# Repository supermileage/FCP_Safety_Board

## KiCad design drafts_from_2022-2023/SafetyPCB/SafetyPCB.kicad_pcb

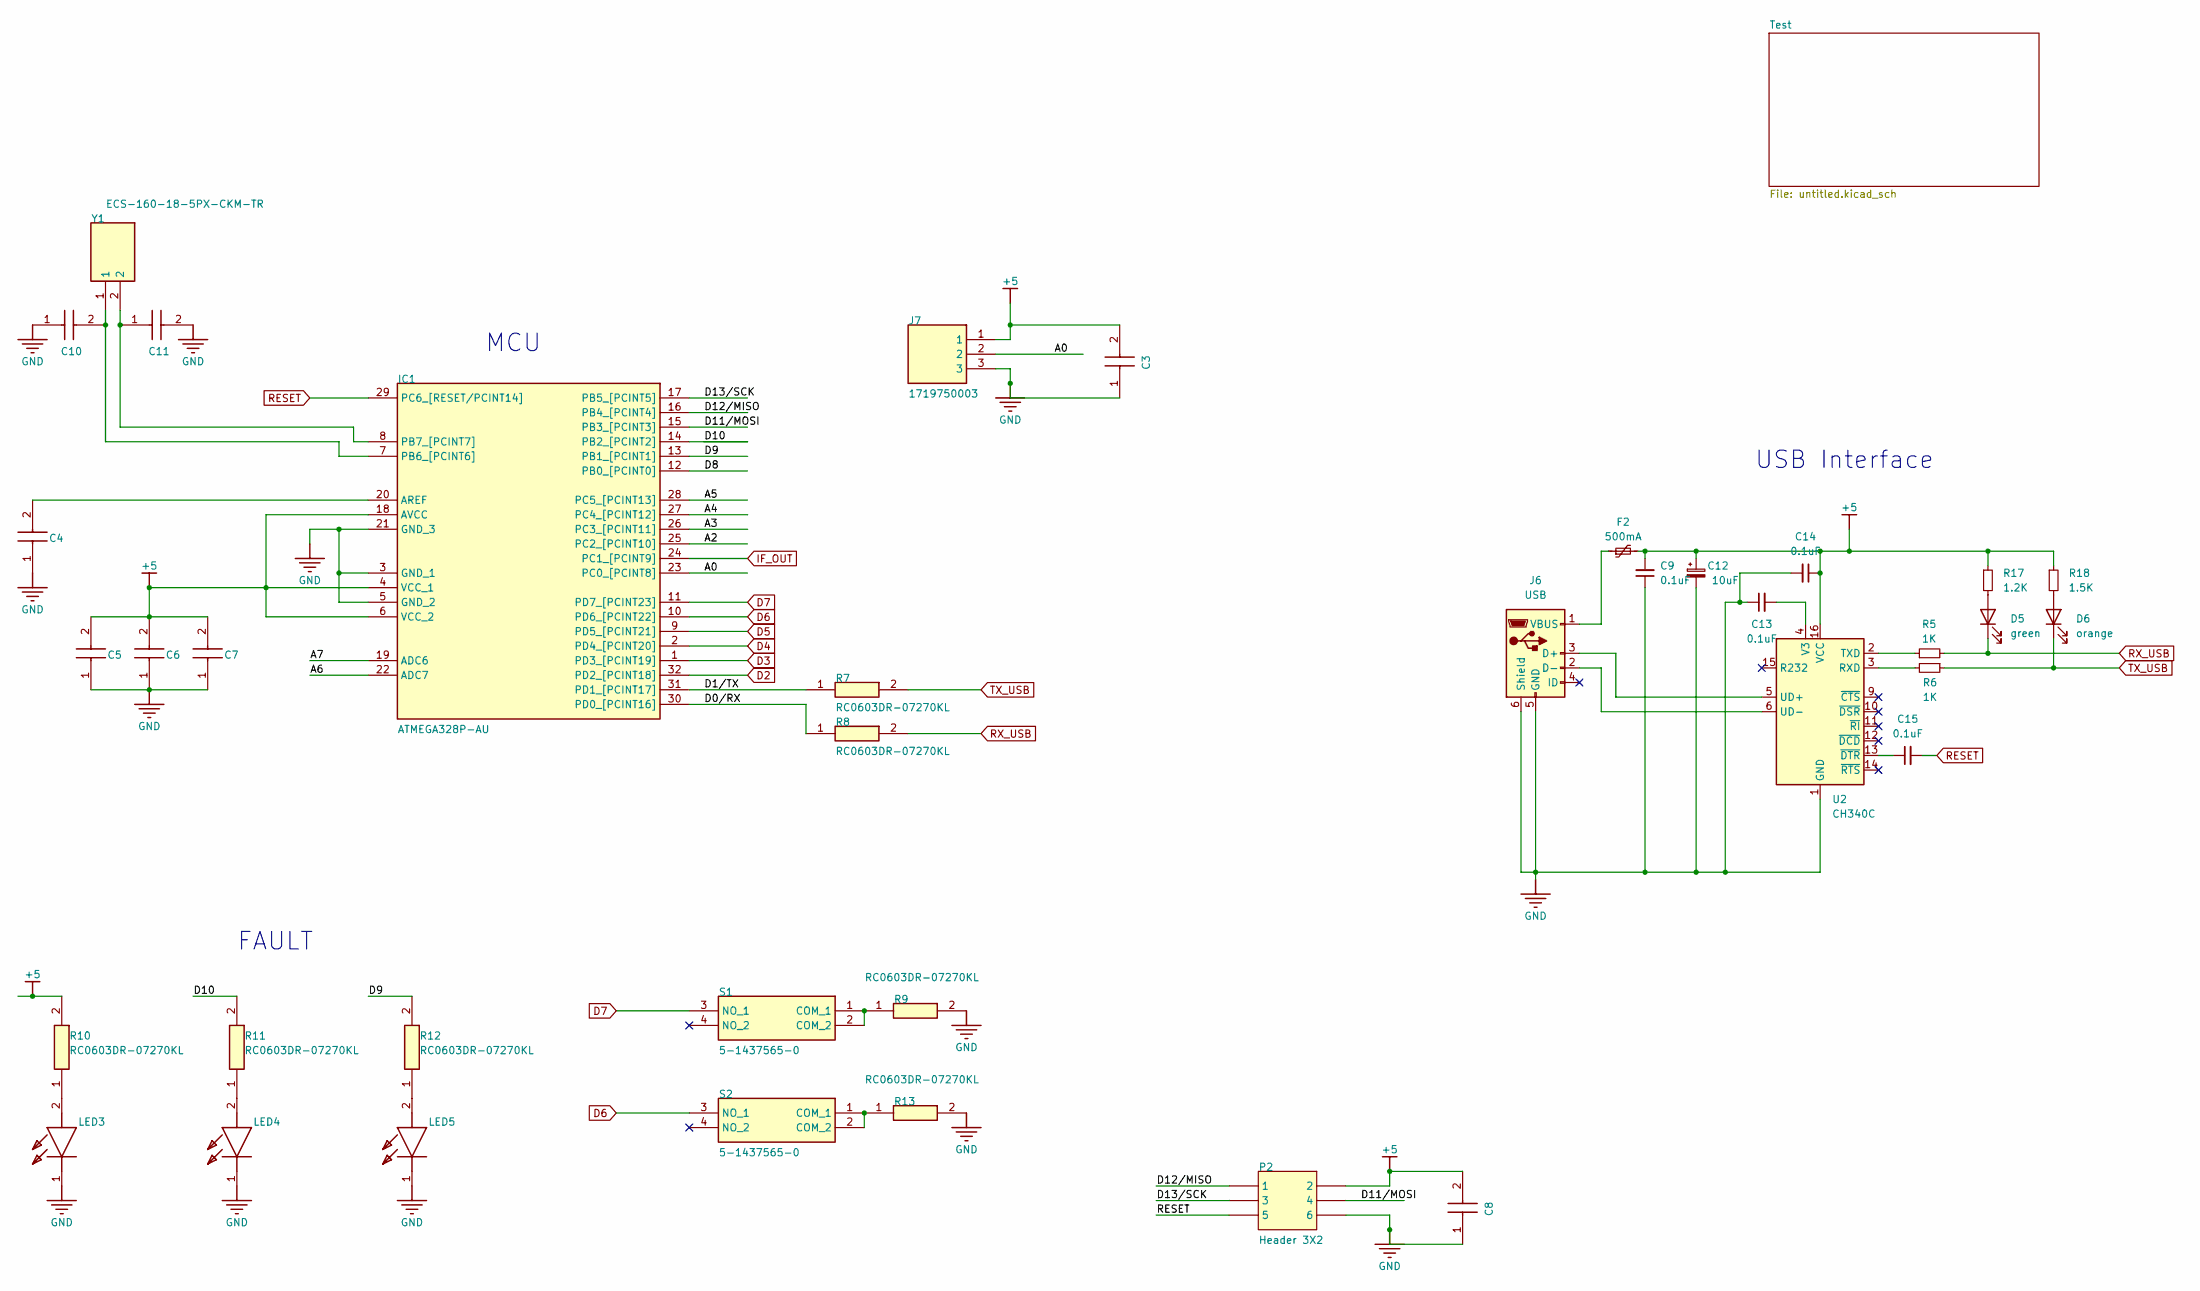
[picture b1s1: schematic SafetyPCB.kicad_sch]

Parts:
C3, C8, C11: 0.1uF; C_0603_1608Metric; MOUSER PART NUMBER 80-C0603C104K3R; digikey part number 399-C0603C104K3RAC7867TR-ND
C4, C5, C6, C7, C10: 0.1uF; C_0603_1608Metric; MOUSER PART NUMBER 80-C0603C104K3R; digikey part number C0603C104K3RACTU
C9, C13, C14, C15: 0.1uF; C_0603_1608Metric
C12: 10uF; C_1206_3216Metric
D5: green; LED_0805_2012Metric
D6: orange; LED_0805_2012Metric
F2: 500mA; Fuse_1206_3216Metric
IC1: ATMEGA328P-AU; QFP80P900X900X120-32N; MANUFACTURER_PART_NUMBER ATMEGA328P-AU; MOUSER PART NUMBER 556-ATMEGA328P-AU
J6: USB; USB_Micro-B_Molex_47346-0001
J7: 1719750003; MOLEX_1719750003; digikey part number 1719750003
LED3, LED4, LED5: LTST-C191TBKT-5A; LED_0201_0603Metric; MOUSER PART NUMBER 859-LTST-C191TBKT-5A; digikey part number LTST-C191TBKT-5A
P2: Header 3X2; PinHeader_2x03_P2.54mm_Vertical
R5, R6: 1K; R_0805_2012Metric
R7, R8, R9, R13: RC0603DR-07270KL; R_0603_1608Metric; digikey part number RC0603DR-07270KL
R10: RC0603DR-07270KL; R_0603_1608Metric; MOUSER PART NUMBER RC0603DR-07270KL-ND - Tape & Reel (TR); digikey part number RC0603DR-07270KL-ND
R11: RC0603DR-07270KL; R_0603_1608Metric; digikey part number RC0603DR-07270KL-ND
R12: RC0603DR-07270KL; R_0603_1608Metric; MANUFACTURER_PART_NUMBER RC0603DR-07270KL; digikey part number RC0603DR-07270KL-ND
R17: 1.2K; R_0805_2012Metric
R18: 1.5K; R_0805_2012Metric
S1, S2: 5-1437565-0; SW_5-1437565-0; MANUFACTURER_PART_NUMBER 5-1437565-0; MOUSER PART NUMBER 506-5-1437565-0
U2: CH340C; SOIC-16_3.9x9.9mm_P1.27mm
Y1: ECS-160-18-5PX-CKM-TR; XTAL_ECS-160-18-5PX-CKM-TR; MANUFACTURER_PART_NUMBER ECS-160-18-5PX-CKM-TR; digikey part number 50-ECS-160-18-5PX-CKM-TR-ND

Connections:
+5: C3.2, C5.2, C6.2, C7.2, C8.2, C9.2, C12.1, C14.1, F2.2, IC1.4 (VCC_1), IC1.6 (VCC_2), IC1.18 (AVCC), J7.1, P2.2, R10.2, R17.1, R18.1, U2.16 (VCC); also elsewhere on the board
/A0: IC1.23 (PC0_[PCINT8]), J7.2
/A2: IC1.25 (PC2_[PCINT10])
/A3: IC1.26 (PC3_[PCINT11])
/A4: IC1.27 (PC4_[PCINT12])
/A5: IC1.28 (PC5_[PCINT13])
/A6: IC1.22 (ADC7)
/A7: IC1.19 (ADC6)
/D0/RX: IC1.30 (PD0_[PCINT16]), R8.1
/D1/TX: IC1.31 (PD1_[PCINT17]), R7.1
/D8: IC1.12 (PB0_[PCINT0])
/D9: IC1.13 (PB1_[PCINT1]), R12.2
/D10: IC1.14 (PB2_[PCINT2]), R11.2
/D11/MOSI: IC1.15 (PB3_[PCINT3]), P2.4
/D12/MISO: IC1.16 (PB4_[PCINT4]), P2.1
/D13/SCK: IC1.17 (PB5_[PCINT5]), P2.3
D2: IC1.32 (PD2_[PCINT18]); also elsewhere on the board
D3: IC1.1 (PD3_[PCINT19]); also elsewhere on the board
D4: IC1.2 (PD4_[PCINT20]); also elsewhere on the board
D5: IC1.9 (PD5_[PCINT21]); also elsewhere on the board
D6: IC1.10 (PD6_[PCINT22]), S2.3 (NO_1)
D7: IC1.11 (PD7_[PCINT23]), S1.3 (NO_1)
GND: C3.1, C4.1, C5.1, C6.1, C7.1, C8.1, C9.1, C10.1, C11.2, C12.2, C13.1, C14.2, IC1.3 (GND_1), IC1.5 (GND_2), IC1.21 (GND_3), J6.5 (GND), J6.6 (Shield), J7.3, LED3.1 (K), LED4.1 (K), LED5.1 (K), P2.6, R9.2, R13.2, U2.1 (GND); also elsewhere on the board
IF_OUT: IC1.24 (PC1_[PCINT9]); also elsewhere on the board
unnamed: C4.2, IC1.20 (AREF)
unnamed: C10.2, IC1.7 (PB6_[PCINT6]), Y1.1
unnamed: C11.1, IC1.8 (PB7_[PCINT7]), Y1.2
unnamed: C13.2, U2.4 (V3)
unnamed: C15.1, U2.13 (~DTR)
unnamed: D5.2 (A), R17.2
unnamed: D6.2 (A), R18.2
unnamed: F2.1, J6.1 (VBUS)
unnamed: J6.2 (D-), U2.6 (UD-)
unnamed: J6.3 (D+), U2.5 (UD+)
unnamed: LED3.2 (A), R10.1
unnamed 45: LED4.2 (A), R11.1; also elsewhere on the board
unnamed 46: LED5.2 (A), R12.1; also elsewhere on the board
unnamed: R5.1, U2.2 (TXD)
unnamed: R6.2, U2.3 (RXD)
unnamed: R9.1, S1.1 (COM_1), S1.2 (COM_2)
unnamed: R13.1, S2.1 (COM_1), S2.2 (COM_2)
RESET: C15.2, IC1.29 (PC6_[RESET/PCINT14]), P2.5
RX_USB: D5.1 (K), R5.2, R8.2
TX_USB: D6.1 (K), R6.1, R7.2

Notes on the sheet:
USB Interface
FAULT
MCU

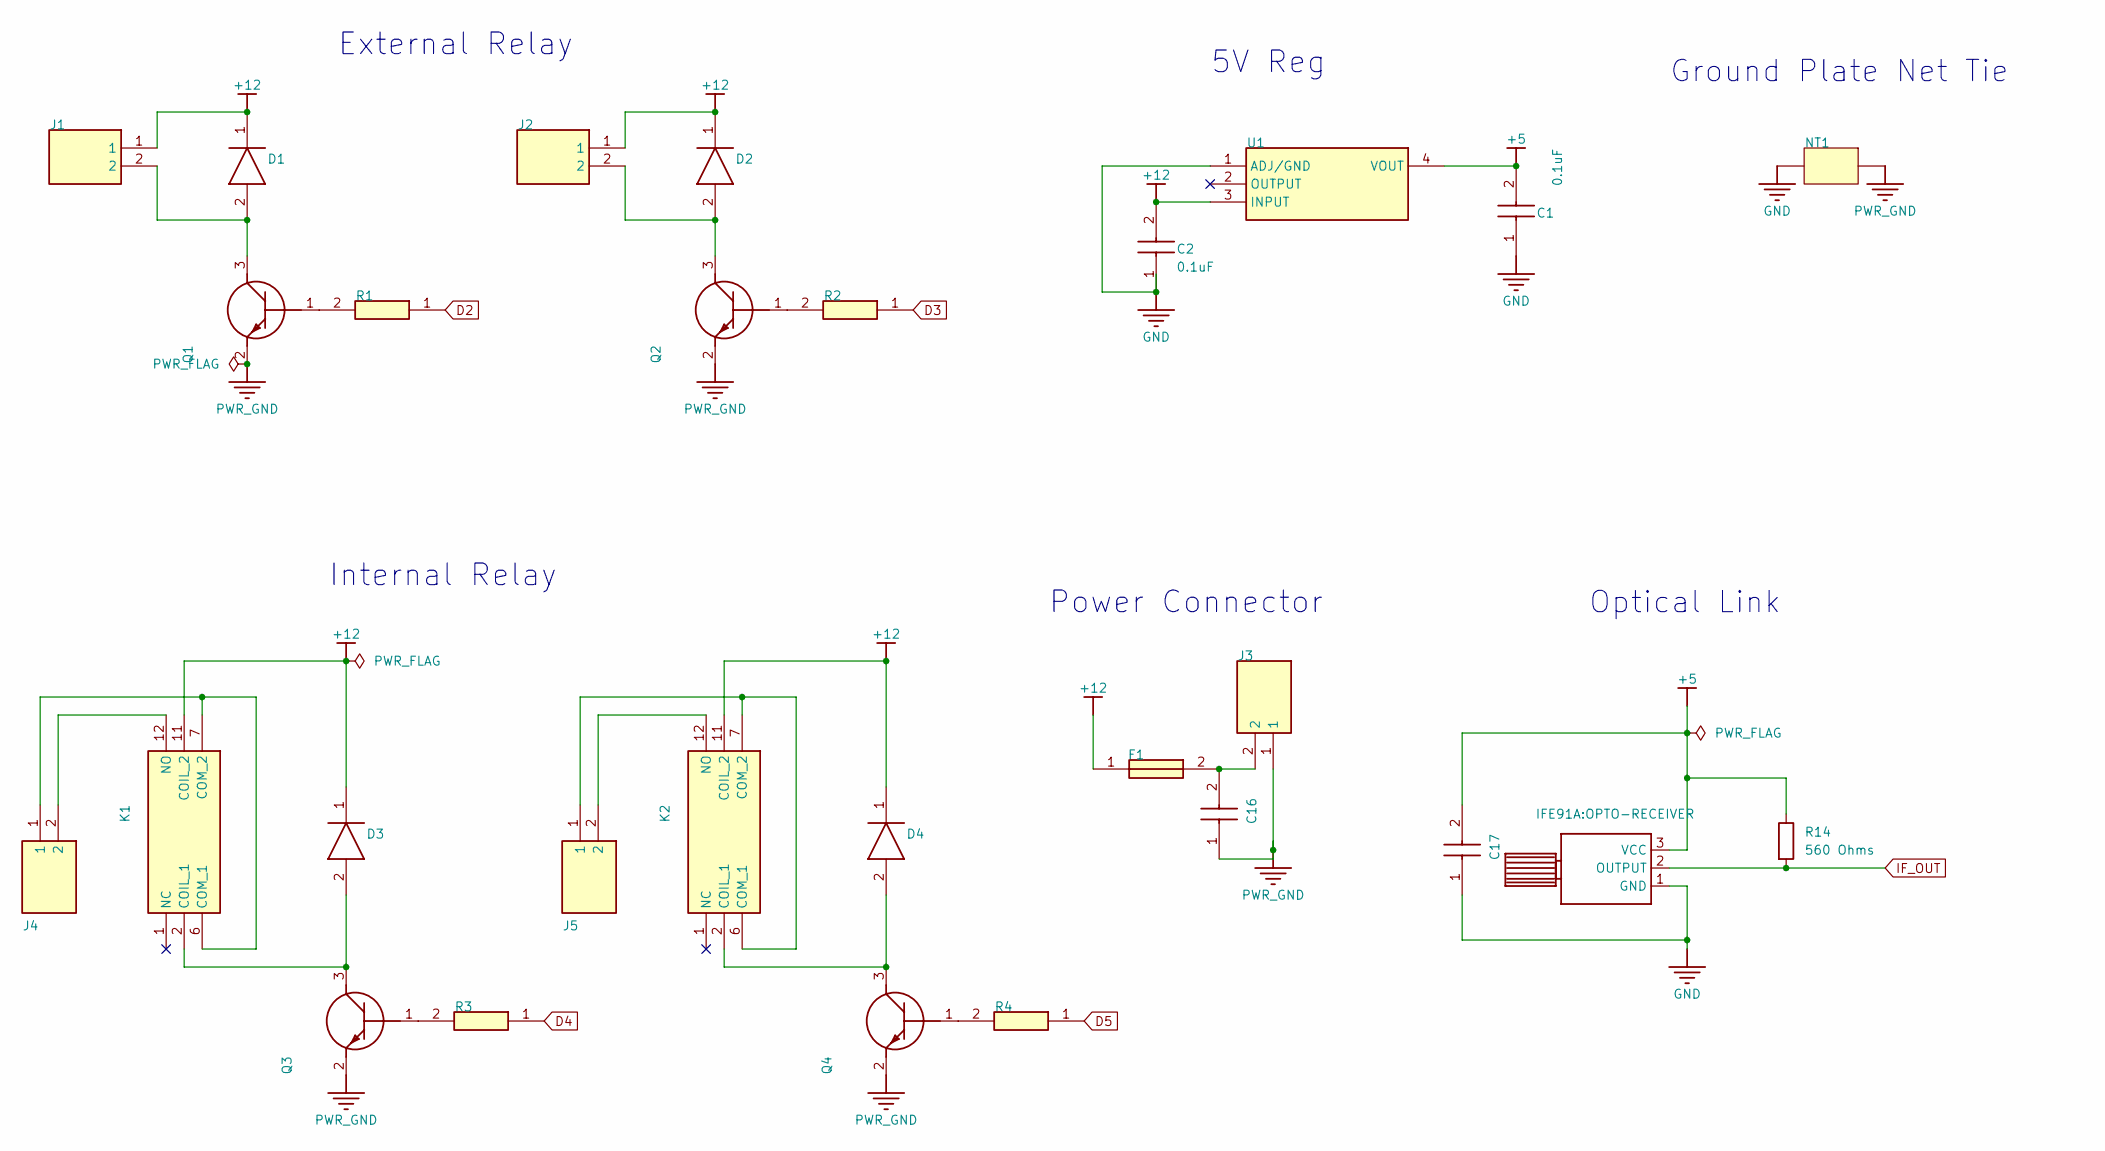
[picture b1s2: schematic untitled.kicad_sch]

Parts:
C1, C2: 0.1uF; C_0603_1608Metric; MOUSER PART NUMBER 80-C0603C104K3R; digikey part number C0603C104K3RACTU
C16, C17: 0.1uF; C_0603_1608Metric; MOUSER PART NUMBER 80-C0603C104K3R; digikey part number 399-C0603C104K3RAC7867TR-ND
D1, D2, D3, D4: DIOM4325X250N_Safety; MOUSER PART NUMBER 512-S1A; digikey part number S1A
F1: FUSE_0154010.DRL; MOUSER PART NUMBER 530-0678H9100-02; digikey part number 0154010.DR
J1: MOLEX_1719750002; MOUSER PART NUMBER 538-171975-0002; digikey part number 171975-0002
J2, J4, J5: MOLEX_1719750002; MANUFACTURER_PART_NUMBER 171975-0002; MOUSER PART NUMBER 538-171975-0002
J3: Molex_Micro-Fit_3.0_43045-0200_2x01_P3.00mm_Horizontal; MANUFACTURER_PART_NUMBER 0430450200; MOUSER PART NUMBER N/A
K1, K2: 1422037-2; MANUFACTURER_PART_NUMBER 1422037-2; MOUSER PART NUMBER 655-1422037-2
NT1: NetTie
Q1, Q2, Q3, Q4: SOT95P237X111-3N; MANUFACTURER_PART_NUMBER BCW66GLT1G; MOUSER PART NUMBER 863-BCW66GLT1G
R1, R2, R3, R4: R_0603_1608Metric; MANUFACTURER_PART_NUMBER RC0603DR-07270KL
R14: 560 Ohms; R_0603_1608Metric
U1: SOT230P700X180-4N; MANUFACTURER_PART_NUMBER LM1117IMPX-5.0/NOPB; MOUSER PART NUMBER 926-LM1117IMPX50NOPB
U$1: IF-D96F; OPTO-RECEIVER

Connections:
+5: C1.2, C17.2, R14.1, U1.4 (VOUT), U$1.3 (VCC); also elsewhere on the board
+12: C2.2, D1.1 (K), D2.1 (K), D3.1 (K), D4.1 (K), F1.1, J1.1, J2.1, K1.11 (COIL_2), K2.11 (COIL_2), U1.3 (INPUT)
D2: R1.1; also elsewhere on the board
D3: R2.1; also elsewhere on the board
D4: R3.1; also elsewhere on the board
D5: R4.1; also elsewhere on the board
GND: C1.1, C2.1, C17.1, NT1.1, U1.1 (ADJ/GND), U$1.1 (GND); also elsewhere on the board
IF_OUT: R14.2, U$1.2 (OUTPUT); also elsewhere on the board
unnamed: C16.2, F1.2, J3.2
unnamed: D1.2 (A), J1.2, Q1.3 (C)
unnamed: D2.2 (A), J2.2, Q2.3 (C)
unnamed: D3.2 (A), K1.2 (COIL_1), Q3.3 (C)
unnamed: D4.2 (A), K2.2 (COIL_1), Q4.3 (C)
unnamed: J4.1, K1.6 (COM_1), K1.7 (COM_2)
unnamed: J4.2, K1.12 (NO)
unnamed: J5.1, K2.6 (COM_1), K2.7 (COM_2)
unnamed: J5.2, K2.12 (NO)
unnamed: Q1.1 (B), R1.2
unnamed: Q2.1 (B), R2.2
unnamed: Q3.1 (B), R3.2
unnamed: Q4.1 (B), R4.2
PWR_GND: C16.1, J3.1, NT1.2, Q1.2 (E), Q2.2 (E), Q3.2 (E), Q4.2 (E)

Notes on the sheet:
Internal Relay
Power Connector
Optical Link
Ground Plate Net Tie
5V Reg
External Relay

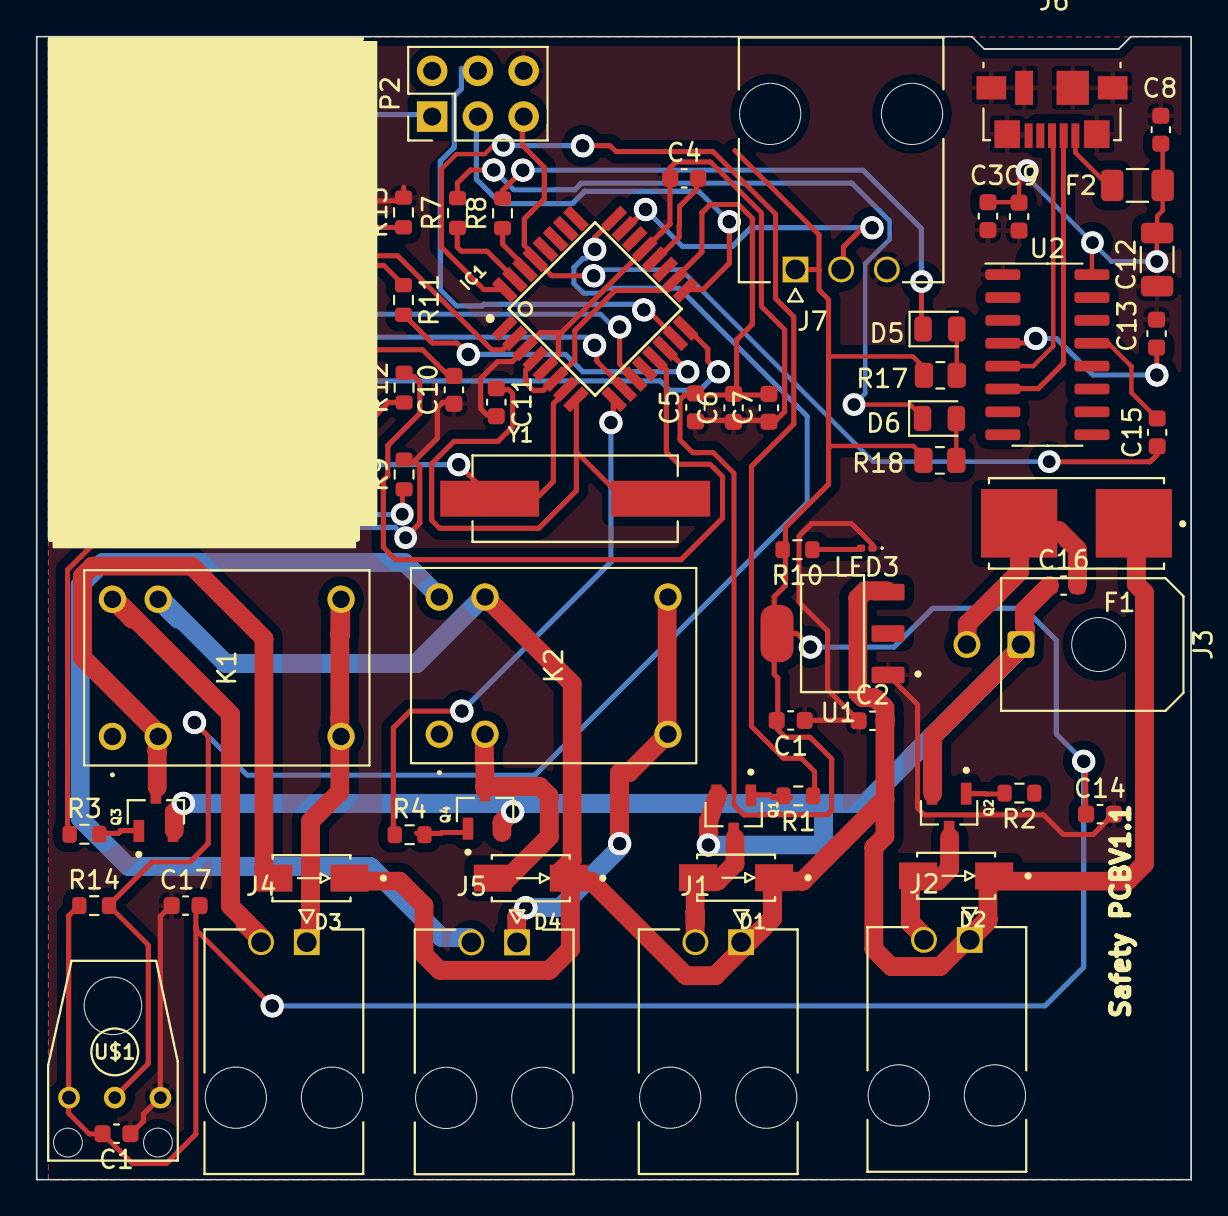
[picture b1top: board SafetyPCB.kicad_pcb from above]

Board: 2 copper layers, 64.2 x 63.5 mm, 66 parts (0 on the bottom side), 50 nets.

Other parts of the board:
C1#2: 0.1uF; C_0603_1608Metric
LED4#2, LED5#2: LTST-C191TBKT-5A; LED_0201_0603Metric

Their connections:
+5: C1#2.2; also elsewhere on the board
GND: C1#2.1, LED4#2.1 (K), LED5#2.1 (K); also elsewhere on the board
unnamed 45: LED4#2.2 (A); also elsewhere on the board
unnamed 46: LED5#2.2 (A); also elsewhere on the board

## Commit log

2022-03-27 update with hydrogen sensor
2023-01-21 version used at SEMA 2022
2023-09-26 Most recent draft I could find - March 2023

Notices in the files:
parts and their libraries:
Copyright 2021 Accelerated Designs. All rights reserved.
